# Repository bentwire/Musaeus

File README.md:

# Musaeus
MC68030 Based SBC 

Simple SBC to learn from.  This board will have the minimal required for a simple computer, 8M SRAM, 8M FLASH, 1M Boot ROM, plus a MPCC for serial, and a PIT For OS timer and generic parallel IO. Hopefully I will be able to port linux to it after I add A DRAM board to the design.

There will be at least one "Expansion" header, I plan on using a 3x150 DIN for this since it will need the entire bus and lots of power and ground lines.  Since I am using a standard connector it means I can also use the pin jumpers I have for my breadboard here as well.

Lots of inspo from:

https://ddraig68k.com/

https://hackaday.io/project/166534-blitz-32bit-68030-homebrew-with-an-isa-bus

I used some of the symbols and footprints from ddraig.

This project is very much a work in progress, and may never be finished...

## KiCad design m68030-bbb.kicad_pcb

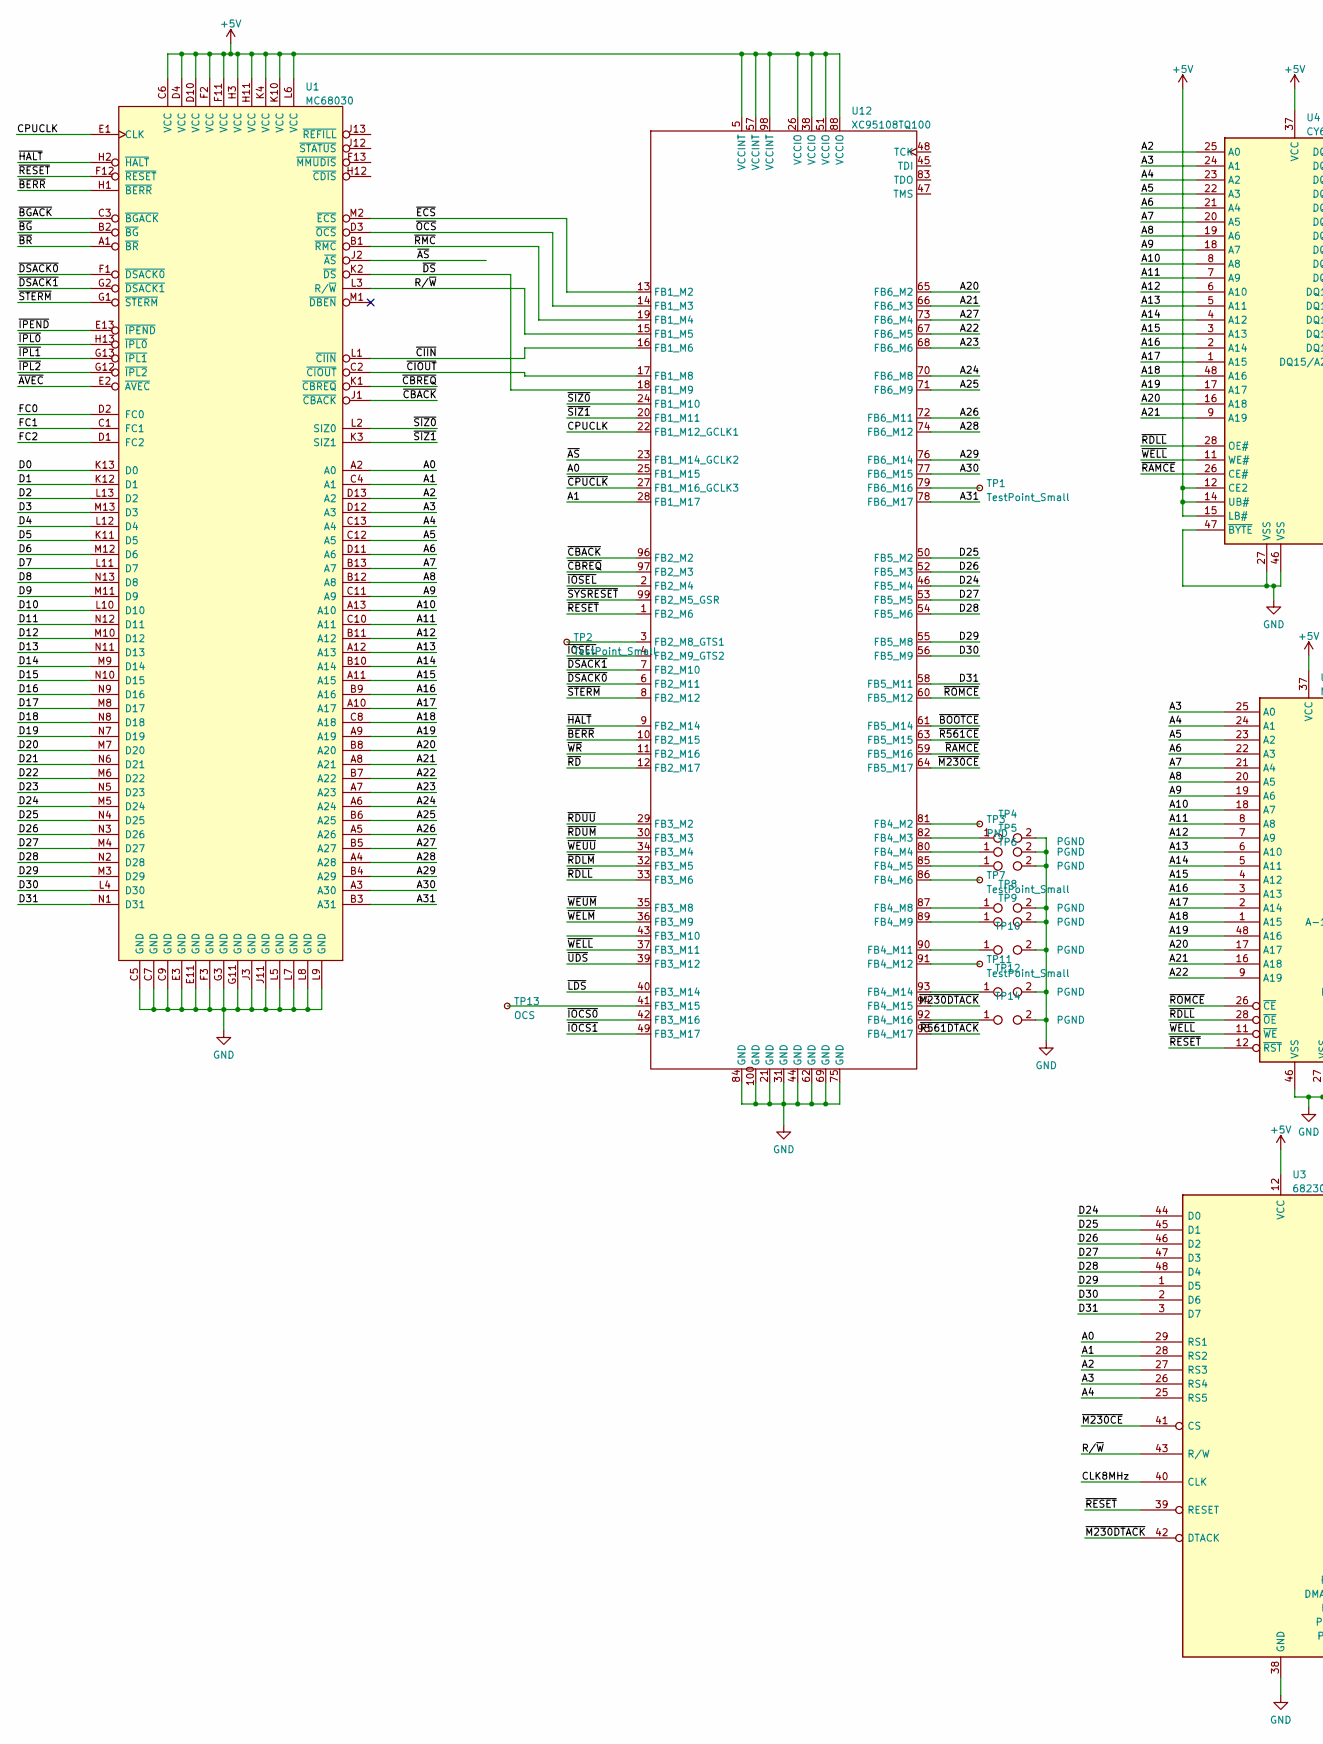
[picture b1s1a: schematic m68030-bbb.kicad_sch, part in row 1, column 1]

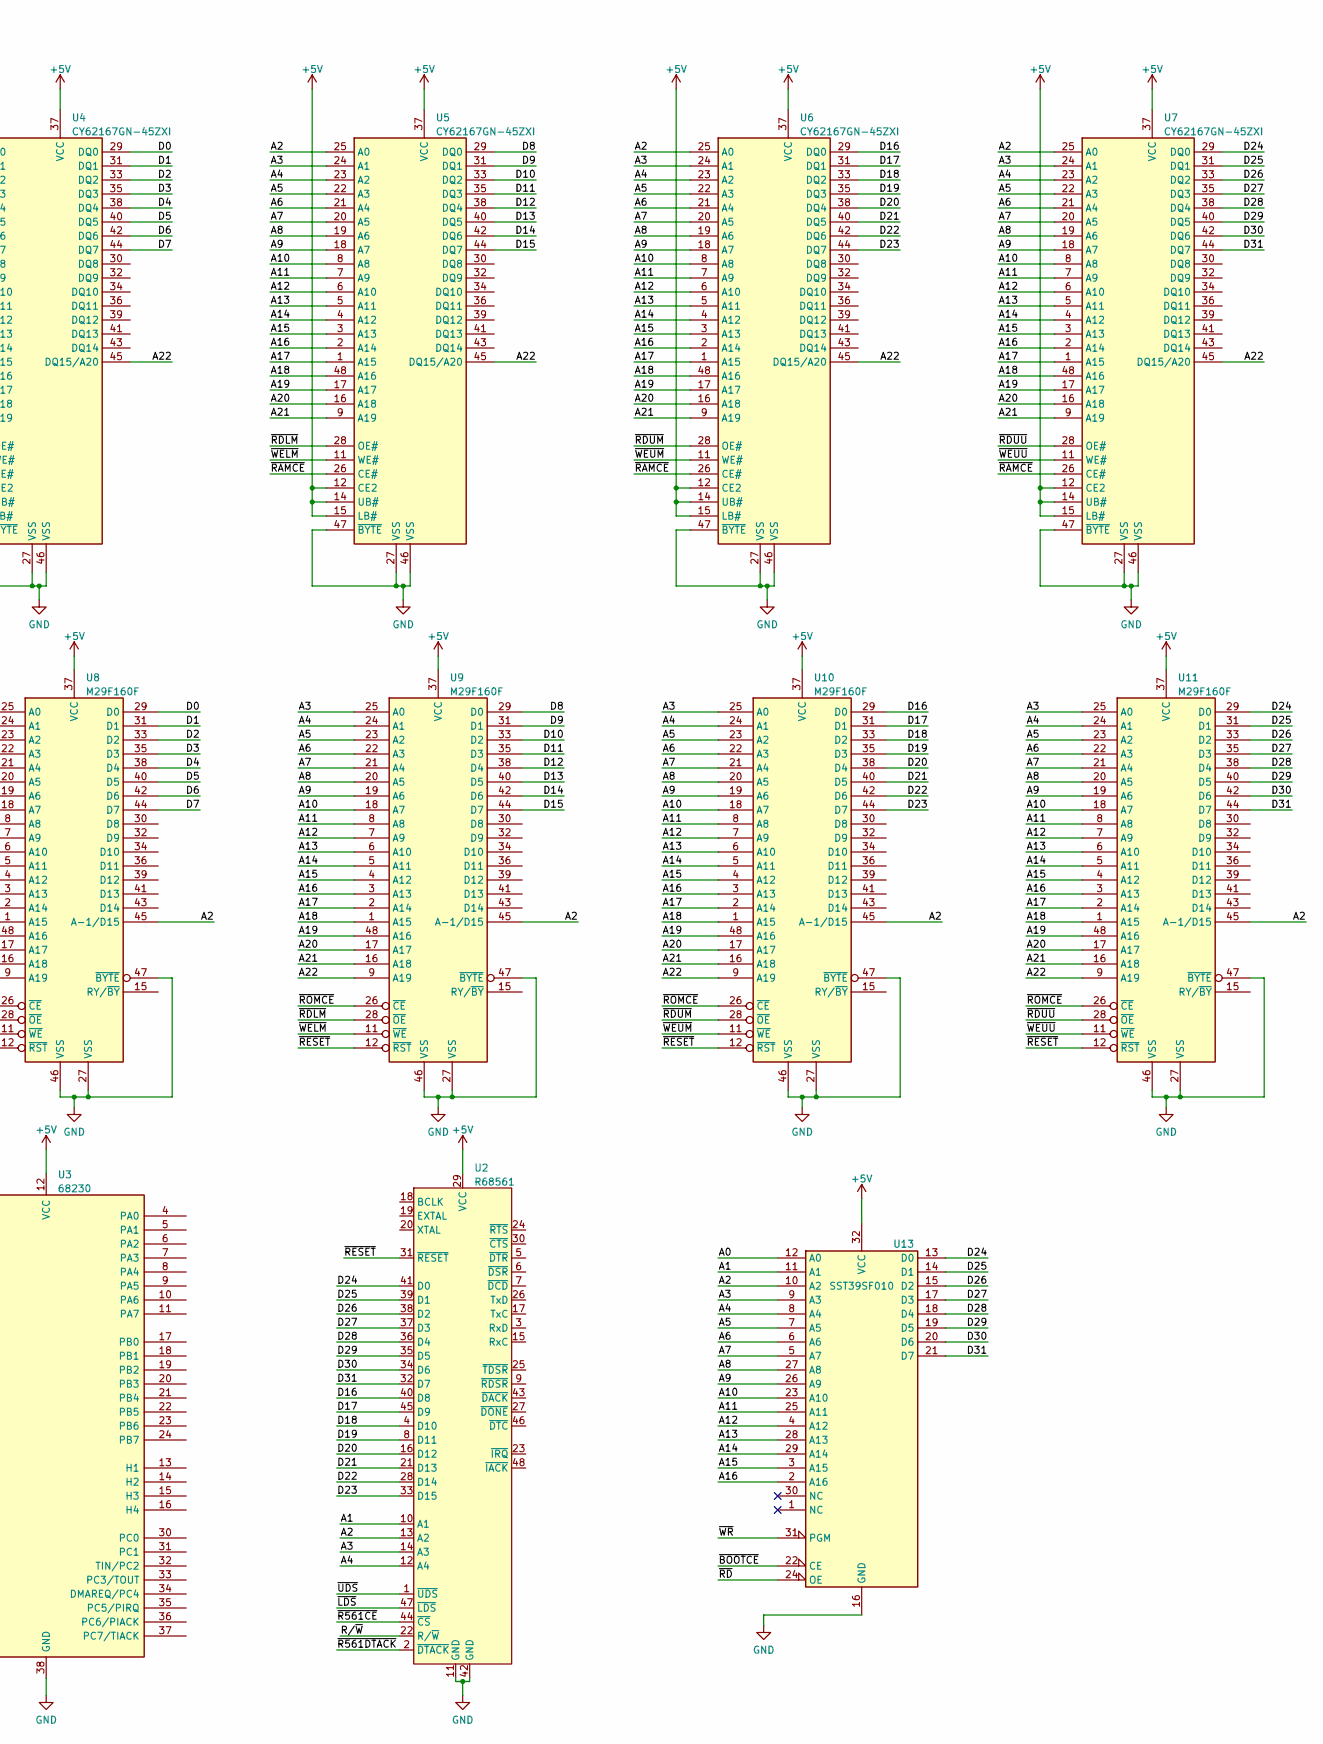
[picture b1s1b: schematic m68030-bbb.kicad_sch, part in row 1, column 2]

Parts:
TP1, TP2, TP7, TP11: TestPoint_Small; TestPoint_Loop_D2.50mm_Drill1.0mm
TP3: PND; TestPoint_Loop_D2.50mm_Drill1.0mm
TP4, TP5, TP6, TP8, TP9, TP10, TP12, TP14: PGND; TestPoint_2Pads_Pitch2.54mm_Drill0.8mm_tie_bottom
TP13: OCS; TestPoint_Loop_D2.50mm_Drill1.0mm
U1: MC68030; MC68030RC
U2: R68561; DIP-48_W15.24mm_Socket_LongPads
U3: 68230; DIP-48_W15.24mm_Socket_LongPads
U4, U5, U6, U7: CY62167GN-45ZXI; TSOP-I-48_18.4x12mm_P0.5mm
U8, U9, U10, U11: M29F160F; TSOP-I-48_18.4x12mm_P0.5mm
U12: XC95108TQ100; TQFP-100_14x14mm_P0.5mm
U13: SST39SF010; DIP-32_W15.24mm_Socket_LongPads

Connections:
+5V: U1.C6 (VCC), U1.D4 (VCC), U1.D10 (VCC), U1.F2 (VCC), U1.F11 (VCC), U1.H3 (VCC), U1.H11 (VCC), U1.K4 (VCC), U1.K10 (VCC), U1.L6 (VCC), U2.29 (VCC), U3.12 (VCC), U4.12 (CE2), U4.14 (UB#), U4.15 (LB#), U4.37 (VCC), U5.12 (CE2), U5.14 (UB#), U5.15 (LB#), U5.37 (VCC), U6.12 (CE2), U6.14 (UB#), U6.15 (LB#), U6.37 (VCC), U7.12 (CE2), U7.14 (UB#), U7.15 (LB#), U7.37 (VCC), U8.37 (VCC), U9.37 (VCC), U10.37 (VCC), U11.37 (VCC), U12.5 (VCCINT), U12.26 (VCCIO), U12.38 (VCCIO), U12.51 (VCCIO), U12.57 (VCCINT), U12.88 (VCCIO), U12.98 (VCCINT), U13.32 (VCC)
/A0: U1.A2 (A0), U3.29 (RS1), U12.25 (FB1_M15), U13.12 (A0)
/A1: U1.C4 (A1), U2.10 (A1), U3.28 (RS2), U12.28 (FB1_M17), U13.11 (A1)
/A2: U1.D13 (A2), U2.13 (A2), U3.27 (RS3), U4.25 (A0), U5.25 (A0), U6.25 (A0), U7.25 (A0), U8.45 (A-1/D15), U9.45 (A-1/D15), U10.45 (A-1/D15), U11.45 (A-1/D15), U13.10 (A2)
/A3: U1.D12 (A3), U2.14 (A3), U3.26 (RS4), U4.24 (A1), U5.24 (A1), U6.24 (A1), U7.24 (A1), U8.25 (A0), U9.25 (A0), U10.25 (A0), U11.25 (A0), U13.9 (A3)
/A4: U1.C13 (A4), U2.12 (A4), U3.25 (RS5), U4.23 (A2), U5.23 (A2), U6.23 (A2), U7.23 (A2), U8.24 (A1), U9.24 (A1), U10.24 (A1), U11.24 (A1), U13.8 (A4)
/A5: U1.C12 (A5), U4.22 (A3), U5.22 (A3), U6.22 (A3), U7.22 (A3), U8.23 (A2), U9.23 (A2), U10.23 (A2), U11.23 (A2), U13.7 (A5)
/A6: U1.D11 (A6), U4.21 (A4), U5.21 (A4), U6.21 (A4), U7.21 (A4), U8.22 (A3), U9.22 (A3), U10.22 (A3), U11.22 (A3), U13.6 (A6)
/A7: U1.B13 (A7), U4.20 (A5), U5.20 (A5), U6.20 (A5), U7.20 (A5), U8.21 (A4), U9.21 (A4), U10.21 (A4), U11.21 (A4), U13.5 (A7)
/A8: U1.B12 (A8), U4.19 (A6), U5.19 (A6), U6.19 (A6), U7.19 (A6), U8.20 (A5), U9.20 (A5), U10.20 (A5), U11.20 (A5), U13.27 (A8)
/A9: U1.C11 (A9), U4.18 (A7), U5.18 (A7), U6.18 (A7), U7.18 (A7), U8.19 (A6), U9.19 (A6), U10.19 (A6), U11.19 (A6), U13.26 (A9)
/A10: U1.A13 (A10), U4.8 (A8), U5.8 (A8), U6.8 (A8), U7.8 (A8), U8.18 (A7), U9.18 (A7), U10.18 (A7), U11.18 (A7), U13.23 (A10)
/A11: U1.C10 (A11), U4.7 (A9), U5.7 (A9), U6.7 (A9), U7.7 (A9), U8.8 (A8), U9.8 (A8), U10.8 (A8), U11.8 (A8), U13.25 (A11)
/A12: U1.B11 (A12), U4.6 (A10), U5.6 (A10), U6.6 (A10), U7.6 (A10), U8.7 (A9), U9.7 (A9), U10.7 (A9), U11.7 (A9), U13.4 (A12)
/A13: U1.A12 (A13), U4.5 (A11), U5.5 (A11), U6.5 (A11), U7.5 (A11), U8.6 (A10), U9.6 (A10), U10.6 (A10), U11.6 (A10), U13.28 (A13)
/A14: U1.B10 (A14), U4.4 (A12), U5.4 (A12), U6.4 (A12), U7.4 (A12), U8.5 (A11), U9.5 (A11), U10.5 (A11), U11.5 (A11), U13.29 (A14)
/A15: U1.A11 (A15), U4.3 (A13), U5.3 (A13), U6.3 (A13), U7.3 (A13), U8.4 (A12), U9.4 (A12), U10.4 (A12), U11.4 (A12), U13.3 (A15)
/A16: U1.B9 (A16), U4.2 (A14), U5.2 (A14), U6.2 (A14), U7.2 (A14), U8.3 (A13), U9.3 (A13), U10.3 (A13), U11.3 (A13), U13.2 (A16)
/A17: U1.A10 (A17), U4.1 (A15), U5.1 (A15), U6.1 (A15), U7.1 (A15), U8.2 (A14), U9.2 (A14), U10.2 (A14), U11.2 (A14)
/A18: U1.C8 (A18), U4.48 (A16), U5.48 (A16), U6.48 (A16), U7.48 (A16), U8.1 (A15), U9.1 (A15), U10.1 (A15), U11.1 (A15)
/A19: U1.A9 (A19), U4.17 (A17), U5.17 (A17), U6.17 (A17), U7.17 (A17), U8.48 (A16), U9.48 (A16), U10.48 (A16), U11.48 (A16)
/A20: U1.B8 (A20), U4.16 (A18), U5.16 (A18), U6.16 (A18), U7.16 (A18), U8.17 (A17), U9.17 (A17), U10.17 (A17), U11.17 (A17), U12.65 (FB6_M2)
/A21: U1.A8 (A21), U4.9 (A19), U5.9 (A19), U6.9 (A19), U7.9 (A19), U8.16 (A18), U9.16 (A18), U10.16 (A18), U11.16 (A18), U12.66 (FB6_M3)
/A22: U1.B7 (A22), U4.45 (DQ15/A20), U5.45 (DQ15/A20), U6.45 (DQ15/A20), U7.45 (DQ15/A20), U8.9 (A19), U9.9 (A19), U10.9 (A19), U11.9 (A19), U12.67 (FB6_M5)
/A23: U1.A7 (A23), U12.68 (FB6_M6)
/A24: U1.A6 (A24), U12.70 (FB6_M8)
/A25: U1.B6 (A25), U12.71 (FB6_M9)
/A26: U1.A5 (A26), U12.72 (FB6_M11)
/A27: U1.B5 (A27), U12.73 (FB6_M4)
/A28: U1.A4 (A28), U12.74 (FB6_M12)
/A29: U1.B4 (A29), U12.76 (FB6_M14)
/A30: U1.A3 (A30), U12.77 (FB6_M15)
/A31: U1.B3 (A31), U12.78 (FB6_M17)
/CLK8MHz: U3.40 (CLK)
/CPUCLK: U1.E1 (CLK), U12.22 (FB1_M12_GCLK1)
/D0: U1.K13 (D0), U4.29 (DQ0), U8.29 (D0)
/D1: U1.K12 (D1), U4.31 (DQ1), U8.31 (D1)
/D2: U1.L13 (D2), U4.33 (DQ2), U8.33 (D2)
/D3: U1.M13 (D3), U4.35 (DQ3), U8.35 (D3)
/D4: U1.L12 (D4), U4.38 (DQ4), U8.38 (D4)
/D5: U1.K11 (D5), U4.40 (DQ5), U8.40 (D5)
/D6: U1.M12 (D6), U4.42 (DQ6), U8.42 (D6)
/D7: U1.L11 (D7), U4.44 (DQ7), U8.44 (D7)
/D8: U1.N13 (D8), U5.29 (DQ0), U9.29 (D0)
/D9: U1.M11 (D9), U5.31 (DQ1), U9.31 (D1)
/D10: U1.L10 (D10), U5.33 (DQ2), U9.33 (D2)
/D11: U1.N12 (D11), U5.35 (DQ3), U9.35 (D3)
/D12: U1.M10 (D12), U5.38 (DQ4), U9.38 (D4)
/D13: U1.N11 (D13), U5.40 (DQ5), U9.40 (D5)
/D14: U1.M9 (D14), U5.42 (DQ6), U9.42 (D6)
/D15: U1.N10 (D15), U5.44 (DQ7), U9.44 (D7)
/D16: U1.N9 (D16), U2.40 (D8), U6.29 (DQ0), U10.29 (D0)
/D17: U1.M8 (D17), U2.45 (D9), U6.31 (DQ1), U10.31 (D1)
/D18: U1.N8 (D18), U2.4 (D10), U6.33 (DQ2), U10.33 (D2)
/D19: U1.N7 (D19), U2.8 (D11), U6.35 (DQ3), U10.35 (D3)
/D20: U1.M7 (D20), U2.16 (D12), U6.38 (DQ4), U10.38 (D4)
/D21: U1.N6 (D21), U2.21 (D13), U6.40 (DQ5), U10.40 (D5)
/D22: U1.M6 (D22), U2.28 (D14), U6.42 (DQ6), U10.42 (D6)
/D23: U1.N5 (D23), U2.33 (D15), U6.44 (DQ7), U10.44 (D7)
/D24: U1.M5 (D24), U2.41 (D0), U3.44 (D0), U7.29 (DQ0), U11.29 (D0), U12.46 (FB5_M4), U13.13 (D0)
/D25: U1.N4 (D25), U2.39 (D1), U3.45 (D1), U7.31 (DQ1), U11.31 (D1), U12.50 (FB5_M2), U13.14 (D1)
/D26: U1.N3 (D26), U2.38 (D2), U3.46 (D2), U7.33 (DQ2), U11.33 (D2), U12.52 (FB5_M3), U13.15 (D2)
/D27: U1.M4 (D27), U2.37 (D3), U3.47 (D3), U7.35 (DQ3), U11.35 (D3), U12.53 (FB5_M5), U13.17 (D3)
/D28: U1.N2 (D28), U2.36 (D4), U3.48 (D4), U7.38 (DQ4), U11.38 (D4), U12.54 (FB5_M6), U13.18 (D4)
/D29: U1.M3 (D29), U2.35 (D5), U3.1 (D5), U7.40 (DQ5), U11.40 (D5), U12.55 (FB5_M8), U13.19 (D5)
/D30: U1.L4 (D30), U2.34 (D6), U3.2 (D6), U7.42 (DQ6), U11.42 (D6), U12.56 (FB5_M9), U13.20 (D6)
/D31: U1.N1 (D31), U2.32 (D7), U3.3 (D7), U7.44 (DQ7), U11.44 (D7), U12.58 (FB5_M11), U13.21 (D7)
/FC0: U1.D2 (FC0)
/FC1: U1.C1 (FC1)
/FC2: U1.D1 (FC2)
/R/~W: U1.L3 (R/~W), U2.22 (R/~W), U3.43 (R/W), U12.15 (FB1_M5)
/~AS: U1.J2 (~AS), U12.23 (FB1_M14_GCLK2)
/~AVEC: U1.E2 (~AVEC)
/~BERR: U1.H1 (~BERR), U12.10 (FB2_M15)
/~BGACK: U1.C3 (~BGACK)
/~BG: U1.B2 (~BG)
/~BOOTCE: U12.61 (FB5_M14), U13.22 (CE)
/~BR: U1.A1 (~BR)
/~CBACK: U1.J1 (~CBACK), U12.96 (FB2_M2)
/~CBREQ: U1.K1 (~CBREQ), U12.97 (FB2_M3)
/~CIIN: U1.L1 (~CIIN), U12.16 (FB1_M6)
/~CIOUT: U1.C2 (~CIOUT), U12.17 (FB1_M8)
/~CPUCLK: U12.27 (FB1_M16_GCLK3)
/~DSACK0: U1.F1 (~DSACK0), U12.6 (FB2_M11)
/~DSACK1: U1.G2 (~DSACK1), U12.7 (FB2_M10)
/~DS: U1.K2 (~DS), U12.18 (FB1_M9)
/~ECS: U1.M2 (~ECS), U12.13 (FB1_M2)
/~HALT: U1.H2 (~HALT), U12.9 (FB2_M14)
/~IOCS0: U12.42 (FB3_M16)
/~IOCS1: U12.49 (FB3_M17)
/~IOSEL: U12.2 (FB2_M4), U12.4 (FB2_M9_GTS2)
/~IPEND: U1.E13 (~IPEND)
/~IPL0: U1.H13 (~IPL0)
/~IPL1: U1.G13 (~IPL1)
/~IPL2: U1.G12 (~IPL2)
/~LDS: U2.47 (~LDS), U12.40 (FB3_M14)
/~M230CE: U3.41 (CS), U12.64 (FB5_M17)
/~M230DTACK: U3.42 (DTACK), U12.94 (FB4_M15)
/~OCS: U1.D3 (~OCS), U12.14 (FB1_M3)
/~R561CE: U2.44 (~CS), U12.63 (FB5_M15)
/~R561DTACK: U2.2 (~DTACK), U12.95 (FB4_M17)
/~RAMCE: U4.26 (CE#), U5.26 (CE#), U6.26 (CE#), U7.26 (CE#), U12.59 (FB5_M16)
/~RDLL: U4.28 (OE#), U8.28 (~OE), U12.33 (FB3_M6)
/~RDLM: U5.28 (OE#), U9.28 (~OE), U12.32 (FB3_M5)
/~RDUM: U6.28 (OE#), U10.28 (~OE), U12.30 (FB3_M3)
/~RDUU: U7.28 (OE#), U11.28 (~OE), U12.29 (FB3_M2)
/~RD: U12.12 (FB2_M17), U13.24 (OE)
/~RESET: U1.F12 (~RESET), U2.31 (~RESET), U3.39 (RESET), U8.12 (~RST), U9.12 (~RST), U10.12 (~RST), U11.12 (~RST), U12.1 (FB2_M6)
/~RMC: U1.B1 (~RMC), U12.19 (FB1_M4)
/~ROMCE: U8.26 (~CE), U9.26 (~CE), U10.26 (~CE), U11.26 (~CE), U12.60 (FB5_M12)
/~SIZ0: U1.L2 (SIZ0), U12.24 (FB1_M10)
/~SIZ1: U1.K3 (SIZ1), U12.20 (FB1_M11)
/~STERM: U1.G1 (~STERM), U12.8 (FB2_M12)
/~SYSRESET: U12.99 (FB2_M5_GSR)
/~UDS: U2.1 (~UDS), U12.39 (FB3_M12)
/~WELL: U4.11 (WE#), U8.11 (~WE), U12.37 (FB3_M11)
/~WELM: U5.11 (WE#), U9.11 (~WE), U12.36 (FB3_M9)
/~WEUM: U6.11 (WE#), U10.11 (~WE), U12.35 (FB3_M8)
/~WEUU: U7.11 (WE#), U11.11 (~WE), U12.34 (FB3_M4)
/~WR: U12.11 (FB2_M16), U13.31 (PGM)
GND: TP4.2, TP5.2, TP6.2, TP8.2, TP9.2, TP10.2, TP12.2, TP14.2, U1.C5 (GND), U1.C7 (GND), U1.C9 (GND), U1.E3 (GND), U1.E11 (GND), U1.F3 (GND), U1.G3 (GND), U1.G11 (GND), U1.J3 (GND), U1.J11 (GND), U1.L5 (GND), U1.L7 (GND), U1.L8 (GND), U1.L9 (GND), U2.11 (GND), U2.42 (GND), U3.38 (GND), U4.27 (VSS), U4.46 (VSS), U4.47 (~BYTE), U5.27 (VSS), U5.46 (VSS), U5.47 (~BYTE), U6.27 (VSS), U6.46 (VSS), U6.47 (~BYTE), U7.27 (VSS), U7.46 (VSS), U7.47 (~BYTE), U8.27 (VSS), U8.46 (VSS), U8.47 (~BYTE), U9.27 (VSS), U9.46 (VSS), U9.47 (~BYTE), U10.27 (VSS), U10.46 (VSS), U10.47 (~BYTE), U11.27 (VSS), U11.46 (VSS), U11.47 (~BYTE), U12.21 (GND), U12.31 (GND), U12.44 (GND), U12.62 (GND), U12.69 (GND), U12.75 (GND), U12.84 (GND), U12.100 (GND), U13.16 (GND)
unnamed: TP1.1, U12.79 (FB6_M16)
unnamed: TP2.1, U12.3 (FB2_M8_GTS1)
unnamed: TP3.1, U12.81 (FB4_M2)
unnamed: TP4.1, U12.82 (FB4_M3)
unnamed: TP5.1, U12.80 (FB4_M4)
unnamed: TP6.1, U12.85 (FB4_M5)
unnamed: TP7.1, U12.86 (FB4_M6)
unnamed: TP8.1, U12.87 (FB4_M8)
unnamed: TP9.1, U12.89 (FB4_M9)
unnamed: TP10.1, U12.90 (FB4_M11)
unnamed: TP11.1, U12.91 (FB4_M12)
unnamed: TP12.1, U12.93 (FB4_M14)
unnamed: TP13.1, U12.41 (FB3_M15)
unnamed: TP14.1, U12.92 (FB4_M16)

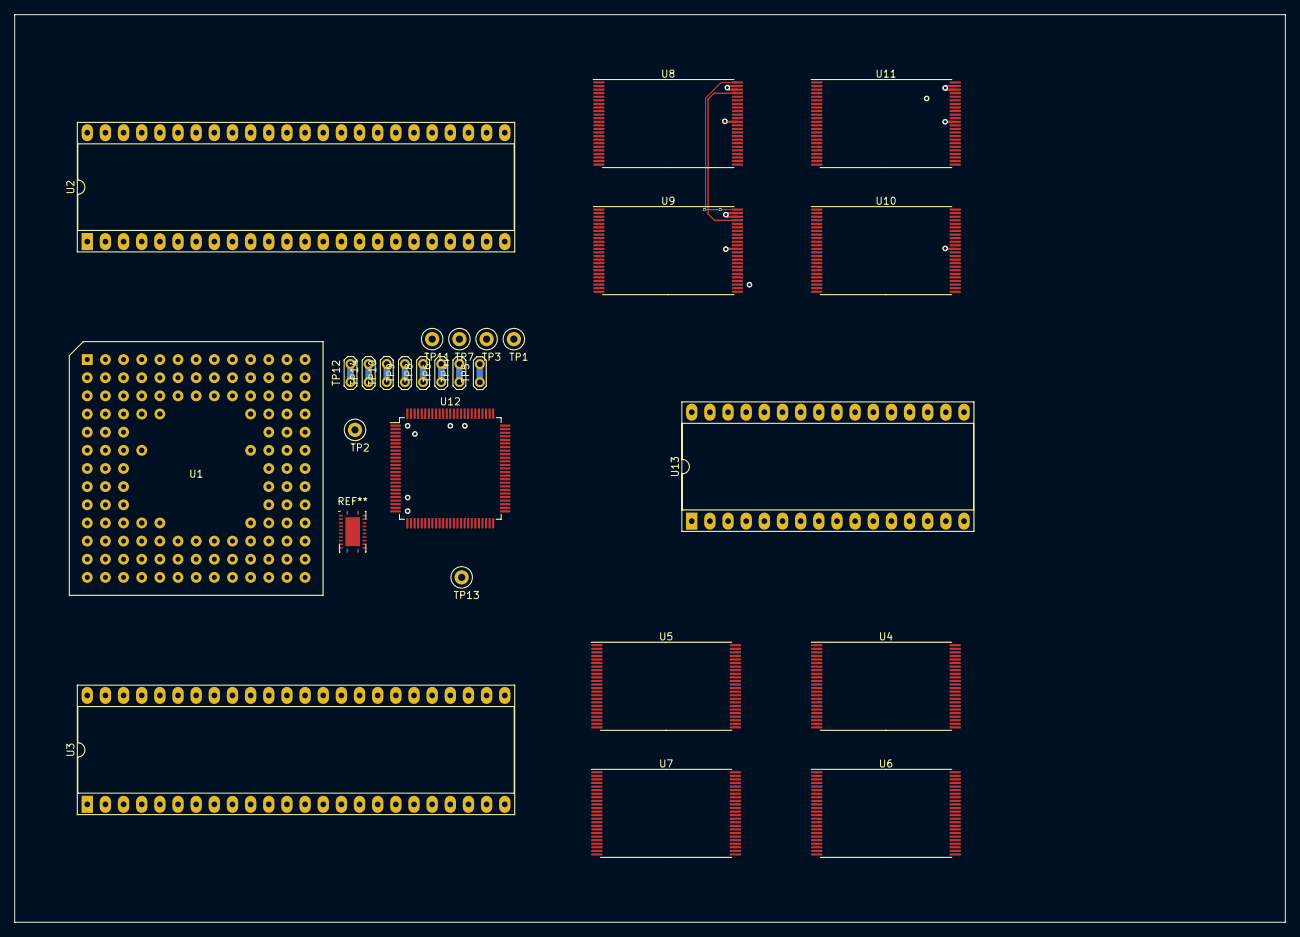
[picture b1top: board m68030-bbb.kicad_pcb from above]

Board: 4 copper layers, 177.8 x 127.0 mm, 27 parts (0 on the bottom side), 119 nets.

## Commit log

2023-01-10 Add MPCC and PIT, move things around. Still need to decide on CPLD to use.
2023-01-12 Messing with the glue chip design.
2023-01-14 More CPLD changes
2023-01-14 More CPLD changes, Boot select logic tested.
2023-01-16 More CPLD changes, started and then dropped the idea of using a state machine for bus state monitoring and dtack generation.
2023-01-18 More CPLD changes, counter and comparitor for DTACK generation testing in sim.
2023-01-21 Filled the CPLD... Not 100% sure this will run at 25MHz... Maybe 20 or 16, design could probably use some optimization.
2023-01-21 Clean up some large files.
2023-01-21 Make sure thet the huge sim files don't get checked in.
2023-01-21 Add some stuff that isn't required to be in repo.
2023-01-21 Remove from repo.
2023-01-21 Update after repo cleanup
2023-01-24 Pretty much finished with the glue logic. Doing intc now.
